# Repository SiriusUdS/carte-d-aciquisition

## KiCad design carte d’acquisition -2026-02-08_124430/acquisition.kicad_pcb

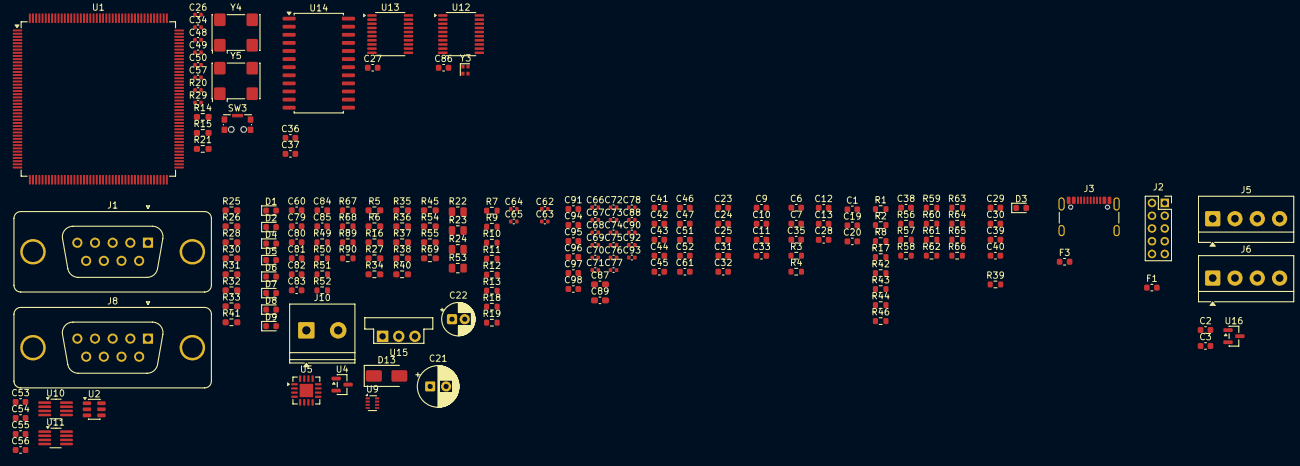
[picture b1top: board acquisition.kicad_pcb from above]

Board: 2 copper layers, 192 parts (0 on the bottom side), 130 nets, no tracks yet.

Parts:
C1, C19, C20: *; C_0603_1608Metric
C2, C3, C12, C13, C94, C95, C96, C97: 1u; C_0603_1608Metric
C6: 0.1uF; C_0603_1608Metric
C7: 10uF; C_0603_1608Metric
C9, C10, C11, C29, C30, C33, C39, C40: 10nF; C_0603_1608Metric
C21: 100uF_25V; CP_Radial_D6.3mm_P2.50mm
C22: 10uF_25V; CP_Radial_D5.0mm_P2.00mm
C23, C24, C25, C31: 2.2u; C_0603_1608Metric
C26, C34, C48, C66, C67, C68, C69, C70, C71, C72, C73, C74, C75, C76, C77, C78, C88, C90, C92, C93: 100n; C_0402_1005Metric
C27, C86: 220n; C_0603_1608Metric
C28, C36: 0.1u; C_0603_1608Metric
C32, C38, C91: 100n; C_0603_1608Metric
C35: 10n; C_0603_1608Metric
C37: 10u; C_0603_1608Metric
C41, C42, C43, C44, C45, C46, C47, C51, C52, C61, C79, C80, C81, C82, C83, C84, C85: C; C_0603_1608Metric
C49, C57: 10u; C_0402_1005Metric
C50: *; C_0402_1005Metric
C53, C55: 100nF; C_0603_1608Metric
C54, C56: 1uF; C_0603_1608Metric
C60: CdV/dT; C_0603_1608Metric
C62, C63, C64, C65: 1u; C_0402_1005Metric
C87, C89: 100n; C_0603_1608Metric_Pad1.08x0.95mm_HandSolder
C98: 4.7u; C_0603_1608Metric
D1, D2, D4, D5, D6, D7, D8, D9: LED; LED_0603_1608Metric
D3: 6.4V; D_0603_1608Metric
D13: SMAJ15A; D_SMA
F1: Fuse; Fuse_0603_1608Metric
F3: Polyfuse; Fuse_0603_1608Metric
J1, J8: DE9_Socket_MountingHoles; DSUB-9_Socket_Vertical_P2.77x2.84mm_MountingHoles
J2: Conn_02x05_Counter_Clockwise; PinSocket_2x05_P2.00mm_Vertical
J3: USB_C_Receptacle_USB2.0_14P; USB_C_Receptacle_GCT_USB4105-xx-A_16P_TopMnt_Horizontal
J5, J6: Screw_Terminal_01x04; TerminalBlock_4Ucon_1x04_P3.50mm_Horizontal
J10: Screw_Terminal_2_P5.00mm; TerminalBlock_Phoenix_PT-1,5-2-5.0-H_1x02_P5.00mm_Horizontal
R1, R2, R7, R8, R9, R10, R11, R12, R13, R17, R18, R19, R42, R43, R44, R46: 1k; R_0603_1608Metric
R3, R4: 5.1k; R_0603_1608Metric
R5, R6, R34, R35, R45, R54, R55: *; R_0603_1608Metric_Pad0.98x0.95mm_HandSolder
R14, R16, R21, R27, R28, R30, R33, R36, R37, R38, R40, R41: 10k; R_0603_1608Metric_Pad0.98x0.95mm_HandSolder
R15: 100k; R_0603_1608Metric_Pad0.98x0.95mm_HandSolder
R20: 10k; C_0402_1005Metric
R22, R23, R24, R53: *; R_0805_2012Metric
R25, R26, R31, R32: 33; R_0603_1608Metric_Pad0.98x0.95mm_HandSolder
R29: 0; C_0402_1005Metric
R39, R61, R62, R63, R64, R65, R66: 10k; R_0603_1608Metric
R49, R50, R51, R52, R67, R68, R89, R90: R_US; R_0603_1608Metric
R56, R57, R58, R59, R60: 22; R_0603_1608Metric
R69: 0; R_0603_1608Metric_Pad0.98x0.95mm_HandSolder
SW3: CK_KMS2xxG; SW_SPST_CK_KMS2xxGP
U1: STM32H747IITx; LQFP-176_24x24mm_P0.5mm
U2: USBLC6-2SC6; SOT-23-6
U4, U16: MCP1799x-500xxTT; SOT-23
U5: INA3221; Texas_RGV0016A_VQFN-16-1EP_4x4mm_P0.65mm_EP2.1x2.1mm
U9: TPS2116DRL; SOT-583-8
U10, U11: TCAN337G; TSOT-23-8_HandSoldering
U12, U13: ADS131M04xPW; TSSOP-20_4.4x6.5mm_P0.65mm
U14: MC74HC4067ADWR2G; SOIC-24W_7.5x15.4mm_P1.27mm
U15: OKI-78SR-5_1.5-W36-C; Converter_DCDC_Murata_OKI-78SR_Vertical
Y3: ASCO; Oscillator_SMD_Abracon_ASCO-4Pin_1.6x1.2mm
Y4: ASV-25.000MHz; Oscillator_SMD_Abracon_ASV-4Pin_7.0x5.1mm
Y5: ASV-32.768kHz; Oscillator_SMD_Abracon_ASV-4Pin_7.0x5.1mm

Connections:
3V3: C28.1, C34.1, C36.1, C37.1, C41.1, C42.1, C43.1, C44.1, C45.1, C46.1, C47.1, C48.1, C49.1, C51.1, C52.1, C53.1, C54.1, C55.1, C56.1, C57.1, C61.1, C63.1, C65.2, C66.1, C67.1, C68.1, C69.1, C70.1, C71.1, C72.1, C73.1, C74.1, C75.1, C76.1, C77.1, C78.1, C83.1, C87.1, C88.1, C89.1, C90.1, C91.1, C92.1, C93.1, C94.1, C95.1, C96.1, C97.1, C98.1, J2.1, R15.1, R20.1, R21.1, R27.2, R28.1, R33.1, R36.2, R37.2, R38.2, R39.1, R40.2, R55.2, R61.1, R62.1, R63.1, R64.1, R65.1, R66.1, U1.7 (VDD), U1.13 (VDD), U1.16 (VDDSMPS), U1.25 (VDD), U1.44 (VDD), U1.48 (VDD), U1.65 (VDD), U1.71 (VDD), U1.82 (VDDLDO), U1.84 (VDD), U1.92 (VDD), U1.99 (VDD), U1.113 (VDD), U1.126 (VDD), U1.135 (VDDLDO), U1.136 (VDD), U1.152 (VDD), U1.160 (VDD), U1.175 (VDDLDO), U1.176 (VDD), U5.2 (IN+3), U5.4 (VS), U10.3 (VCC), U11.3 (VCC), U12.20 (DVDD), U13.20 (DVDD), U14.24 (VCC), Y4.4 (Vdd), Y5.4 (Vdd)
3V3A: C1.1, C13.1, C19.1, C20.1, C62.2, C64.2, U1.39 (VREF+), U1.40 (VDDA), U4.2 (VO), U5.15 (IN+2), U12.1 (AVDD), U13.1 (AVDD)
5V: C81.1, R54.2, R90.1, U9.2 (VOUT), U9.7 (VOUT)
5VA: C3.1, J5.1, J6.1, U5.12 (IN+1), U16.2 (VO)
5V_BAT: R22.2, R24.2, R34.2, U9.3 (VIN1), U15.3 (OUT)
5V_USB: R35.2, U9.6 (VIN2)
12.8V: C2.1, C12.1, R69.2, U4.3 (VI), U15.1 (IN), U16.3 (VI)
12.8V_BAT: C21.1, C22.1, D13.1 (A1), F1.2, R51.1, R53.2, R69.1
+5V: C6.1, C7.1, D3.1 (K), F3.2, U2.5 (VBUS)
/ADS131/+IN2: C9.2, J5.2, R1.2
/ADS131/+IN3: C10.2, J6.2, R8.2
/ADS131/+IN4: C11.2, R42.2
/ADS131/+IN5: C33.2, R44.2
/ADS131/-IN2: C9.1, J5.3, R2.2
/ADS131/-IN3: C10.1, J6.3, R17.2
/ADS131/-IN4: C11.1, R43.2
/ADS131/-IN5: C33.1, R46.2
/ADS131/ADS_CS: U1.49 (PA4), U12.12 (~CS)
/ADS131/ADS_DIN: U1.52 (PA7), U12.16 (DIN)
/ADS131/ADS_DOUT: U1.51 (PA6), U12.15 (DOUT)
/ADS131/ADS_SCLK: U1.50 (PA5), U12.14 (SCLK)
/ADS131/ADS_SYNC/RESET: U1.154 (PG10), U12.11 (~SYNC/~RESET)
/Communication/CAN.FAULT: R28.2, R33.2, U10.5 (FAULT), U11.5 (FAULT)
/Communication/CAN_N: J1.2, J8.2, U10.6 (CANL), U11.6 (CANL)
/Communication/CAN_P: J1.7, J8.7, U10.7 (CANH), U11.7 (CANH)
/Microcontrolleur/ADC_4theromocouple: U1.155 (PG11), U13.11 (~SYNC/~RESET)
/Microcontrolleur/BC0: U1.156 (PG12), U14.10 (S0)
/Microcontrolleur/BC1: U1.157 (PG13), U14.11 (S1)
/Microcontrolleur/BC2: U1.158 (PG14), U14.14 (S2)
/Microcontrolleur/BC3: U1.161 (PG15), U14.13 (S3)
/Microcontrolleur/Boot: R14.2, U1.167 (BOOT0)
/Microcontrolleur/CAN.RXD: R26.1, R32.1, U1.169 (PB9)
/Microcontrolleur/CAN.TXD: R25.1, R31.1, U1.168 (PB8)
/Microcontrolleur/Clock_25Mhz: C50.1, R29.2
/Microcontrolleur/I2C1_SCL: R40.1, U1.165 (PB6), U5.6 (SCL)
/Microcontrolleur/I2C1_SDA: R38.1, U1.166 (PB7), U5.7 (SDA)
/Microcontrolleur/NRST: C26.1, J2.6, R15.2, SW3.2, U1.33 (NRST)
/Microcontrolleur/PE13: R27.1, U1.75 (PE13), U5.9 (CRITICAL)
/Microcontrolleur/PE14: R37.1, U1.76 (PE14), U5.13 (TC)
/Microcontrolleur/PE15: R36.1, U1.77 (PE15), U5.8 (WARNING)
/Microcontrolleur/SD.CLK: R58.1, U1.142 (PC12)
/Microcontrolleur/SD.CMD: R63.2, U1.145 (PD2)
/Microcontrolleur/SD.DAT0: R59.1, U1.124 (PC8)
/Microcontrolleur/SD.DAT1: R60.1, U1.125 (PC9)
/Microcontrolleur/SD.DAT2: R56.1, U1.140 (PC10)
/Microcontrolleur/SD.DAT3: R57.1, U1.141 (PC11)
/Microcontrolleur/SD.DET: R66.2, U1.116 (PG6)
/Microcontrolleur/SPI5_MISO: U1.28 (PF8), U13.15 (DOUT)
/Microcontrolleur/SPI5_MOSI: U1.29 (PF9), U13.16 (DIN)
/Microcontrolleur/SPI5_NSS: U1.26 (PF6), U13.12 (~CS)
/Microcontrolleur/SPI5_SCK: U1.27 (PF7), U13.14 (SCLK)
/Microcontrolleur/SWCLK: J2.9, U1.138 (PA14)
/Microcontrolleur/SWDIO: J2.10, U1.132 (PA13)
/Microcontrolleur/SWO: J2.8, U1.162 (PB3)
/Microcontrolleur/led0: R5.2, U1.66 (PG1)
/Microcontrolleur/led1: R6.2, U1.110 (PG2)
/Microcontrolleur/led2: R45.2, U1.111 (PG3)
GND: C1.2, C2.2, C3.2, C6.2, C7.2, C12.2, C13.2, C19.2, C20.2, C21.2, C22.2, C23.2, C24.2, C25.2, C26.2, C27.1, C28.2, C31.2, C32.2, C34.2, C35.2, C36.2, C37.2, C38.2, C41.2, C42.2, C43.2, C44.2, C45.2, C46.2, C47.2, C48.2, C49.2, C50.2, C51.2, C52.2, C53.2, C54.2, C55.2, C56.2, C57.2, C60.2, C61.2, C62.1, C63.2, C64.1, C65.1, C66.2, C67.2, C68.2, C69.2, C70.2, C71.2, C72.2, C73.2, C74.2, C75.2, C76.2, C77.2, C78.2, C81.2, C82.2, C83.2, C84.2, C85.2, C86.1, C87.2, C88.2, C89.2, C90.2, C91.2, C92.2, C93.2, C94.2, C95.2, C96.2, C97.2, C98.2, D1.1 (K), D2.1 (K), D3.2 (A), D4.1 (K), D5.1 (K), D6.1 (K), D7.1 (K), D8.1 (K), D9.1 (K), D13.2 (A2), J1.0 (PAD), J1.3, J2.2, J2.3, J2.5, J3.A1 (GND), J3.A12 (GND), J3.B1 (GND), J3.B12 (GND), J5.4, J6.4, J8.0 (PAD), J8.3, J10.1, R3.2, R4.2, R23.1, R30.2, R41.2, R49.2, R52.2, R67.2, R89.2, SW3.1, SW3.SH (B), U1.6 (VSS), U1.12 (VSS), U1.14 (VSSSMPS), U1.24 (VSS), U1.38 (VSSA), U1.45 (VSS), U1.47 (VSS), U1.64 (VSS), U1.70 (VSS), U1.81 (VSS), U1.83 (VSS), U1.93 (VSS), U1.100 (VSS), U1.103 (DSI_D0P), U1.104 (DSI_D0N), U1.105 (VSSDSI), U1.106 (DSI_CKP), U1.107 (DSI_CKN), U1.109 (VSSDSI), U1.112 (VSS), U1.119 (VSS), U1.134 (VSS), U1.137 (VSS), U1.151 (VSS), U1.159 (VSS), U1.173 (VSS), U2.2 (GND), U4.1 (GND), U5.1 (IN-3), U5.3 (GND), U5.5 (A0), U5.11 (IN-1), U5.14 (IN-2), U5.17 (EP), U9.1 (GND), U10.2 (GND), U11.2 (GND), U14.12 (GND), U14.15 (~E), U14.16 (I15), U14.17 (I14), U14.18 (I13), U14.19 (I12), U14.20 (I11), U14.21 (I10), U15.2 (GND), U16.1 (GND), Y3.2 (GND), Y4.2 (GND), Y5.2 (GND)
GNDA: U12.2 (AGND), U12.19 (DGND), U13.2 (AGND), U13.19 (DGND)
unnamed: C24.1, U1.172 (VCAP)
unnamed: C25.1, U1.133 (VCAP)
unnamed: C31.1, U1.80 (VCAP)
unnamed: C85.1, R50.2
unnamed: D1.2 (A), R34.1
unnamed: D2.2 (A), R53.1
unnamed: D4.2 (A), R54.1
unnamed: D5.2 (A), R55.1
unnamed: D6.2 (A), R35.1
unnamed: D7.2 (A), R5.1
unnamed: D8.2 (A), R6.1
unnamed: D9.2 (A), R45.1
unnamed: F1.1, J10.2
unnamed: F3.1, J3.A4 (VBUS), J3.A9 (VBUS), J3.B4 (VBUS), J3.B9 (VBUS)
unnamed: R51.2, R52.1
unnamed: J3.A5 (CC1), R4.1
unnamed: J3.B5 (CC2), R3.1
unnamed: J3.A6 (D+), J3.B6 (D+), U2.3 (I/O2)
unnamed: J3.A7 (D-), J3.B7 (D-), U2.1 (I/O1)
unnamed: C35.1, J3.S1 (SHIELD)
unnamed: R59.2, R64.2
unnamed: R60.2, R65.2
unnamed: R56.2, R61.2
unnamed: R57.2, R62.2
unnamed: R39.2, U1.174 (PDR_ON)
unnamed: C32.1, U1.8 (VBAT)
unnamed: C23.1, U1.101 (VCAPDSI)
unnamed: C84.1, R50.1
unnamed: R89.1, R90.2
unnamed: R16.1, U5.10 (PV)
unnamed: R16.2, U5.16 (VPU)
unnamed: R22.1, R23.2, U9.4 (PR1)
unnamed: R24.1, U9.8 (ST)
unnamed: R26.2, U10.4 (RXD)
unnamed: R30.1, U10.8 (S)
unnamed: R25.2, U10.1 (TXD)
unnamed: R32.2, U11.4 (RXD)
unnamed: R41.1, U11.8 (S)
unnamed: R31.2, U11.1 (TXD)
unnamed: R2.1, U12.4 (AIN0N)
unnamed: R1.1, U12.3 (AIN0P)
unnamed: R17.1, U12.5 (AIN1N)
unnamed: R8.1, U12.6 (AIN1P)
unnamed: R43.1, U12.8 (AIN2N)
unnamed: R42.1, U12.7 (AIN2P)
unnamed: R46.1, U12.9 (AIN3N)
unnamed: R44.1, U12.10 (AIN3P)
unnamed: C86.2, U12.18 (CAP)
unnamed: R9.1, U13.4 (AIN0N)
unnamed: R7.1, U13.3 (AIN0P)
unnamed: R11.1, U13.5 (AIN1N)
unnamed: R10.1, U13.6 (AIN1P)
unnamed: R13.1, U13.8 (AIN2N)
unnamed: R12.1, U13.7 (AIN2P)
unnamed: R19.1, U13.9 (AIN3N)
unnamed: R18.1, U13.10 (AIN3P)
unnamed: C27.2, U13.18 (CAP)
unnamed: Y3.1 (Tri-State), Y3.4 (VDD)
unnamed: R20.2, Y4.1 (EN)
unnamed: R29.1, Y4.3 (OUT)
unnamed: R21.2, Y5.1 (EN)
USBC.DM: U1.130 (PA11), U2.6 (I/O1)
USBC.DP: U1.131 (PA12), U2.4 (I/O2)
capteur_1+: C29.2, R7.2
capteur_1-: C29.1, R9.2, U14.9 (I0)
capteur_2+: C30.2, R10.2
capteur_2-: C30.1, R11.2, U14.8 (I1)
capteur_3+: C39.2, R12.2
capteur_3-: C39.1, R13.2, U14.7 (I2)
capteur_4+: C40.2, R18.2
capteur_4-: C40.1, R19.2, U14.6 (I3)

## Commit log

2026-02-15 Mise à jour du schéma
    Bon schéma de la fill et enlevé les parties non utilisées
2026-02-15 Ajout clock et alim
    Ajout de la clock et l'alim mais sans les schéma. Juste les fils
2026-02-15 Feuille de plus et modifs de l'alim
    J'ai ajouté une feuille pour le power et j'ai modifié les ldos et le buck mais il faut repasser dessus
2026-02-16 thermocouple
2026-02-17 vince
2026-02-21 Power et maj can et sd
    Modifications sur l'alim selon le schéma sur Canvas et mise à jour du can et carte sd
2026-02-23 STM et ADS131 dans des feuilles
2026-02-24 Petits ajustements
2026-02-24 arthur net
2026-02-25 arthur
2026-02-26 Mis a jour plusieurs circuit et ajouter beaucoup de footprint manquant
2026-03-04 Ajout du 5VA et des borniers a vis pour loadcell
